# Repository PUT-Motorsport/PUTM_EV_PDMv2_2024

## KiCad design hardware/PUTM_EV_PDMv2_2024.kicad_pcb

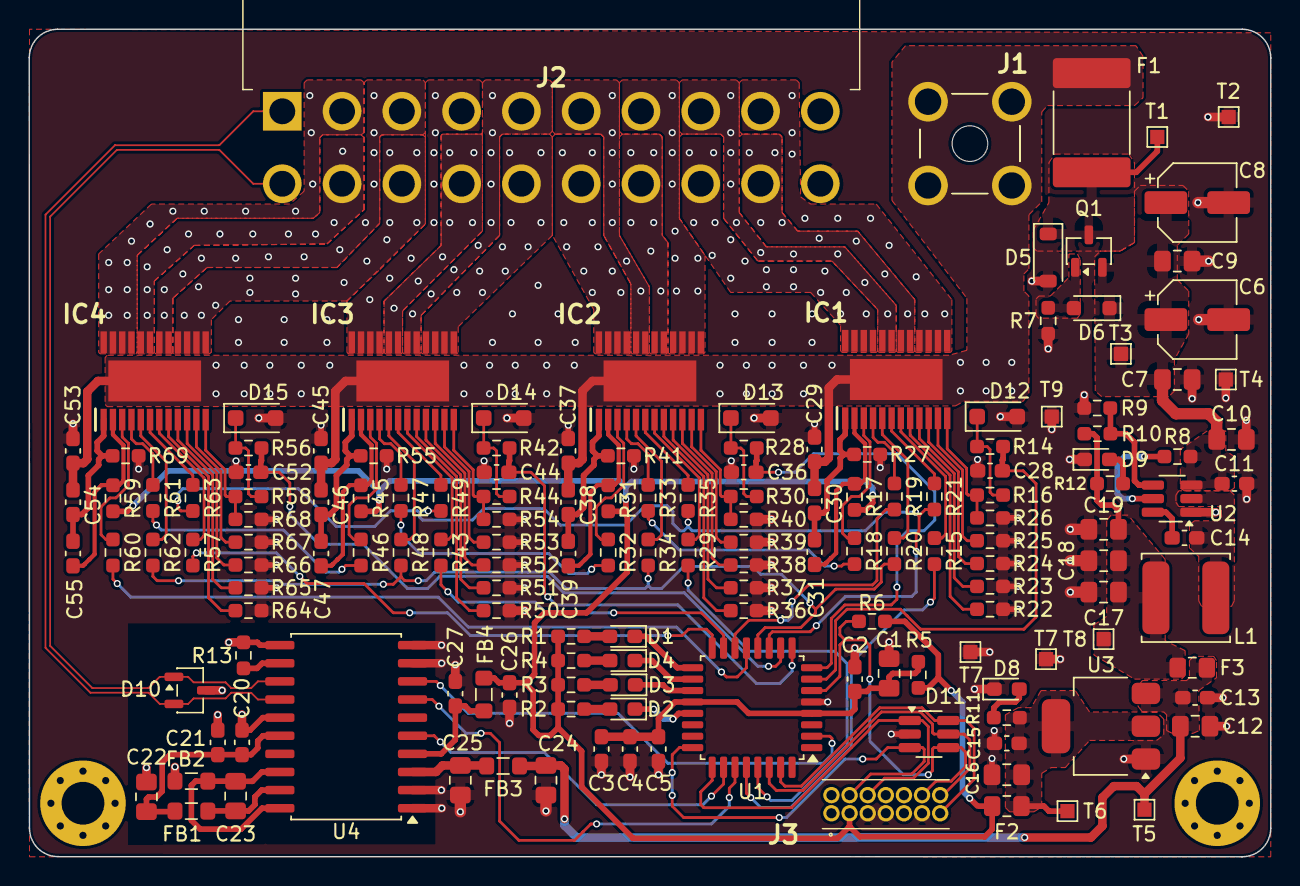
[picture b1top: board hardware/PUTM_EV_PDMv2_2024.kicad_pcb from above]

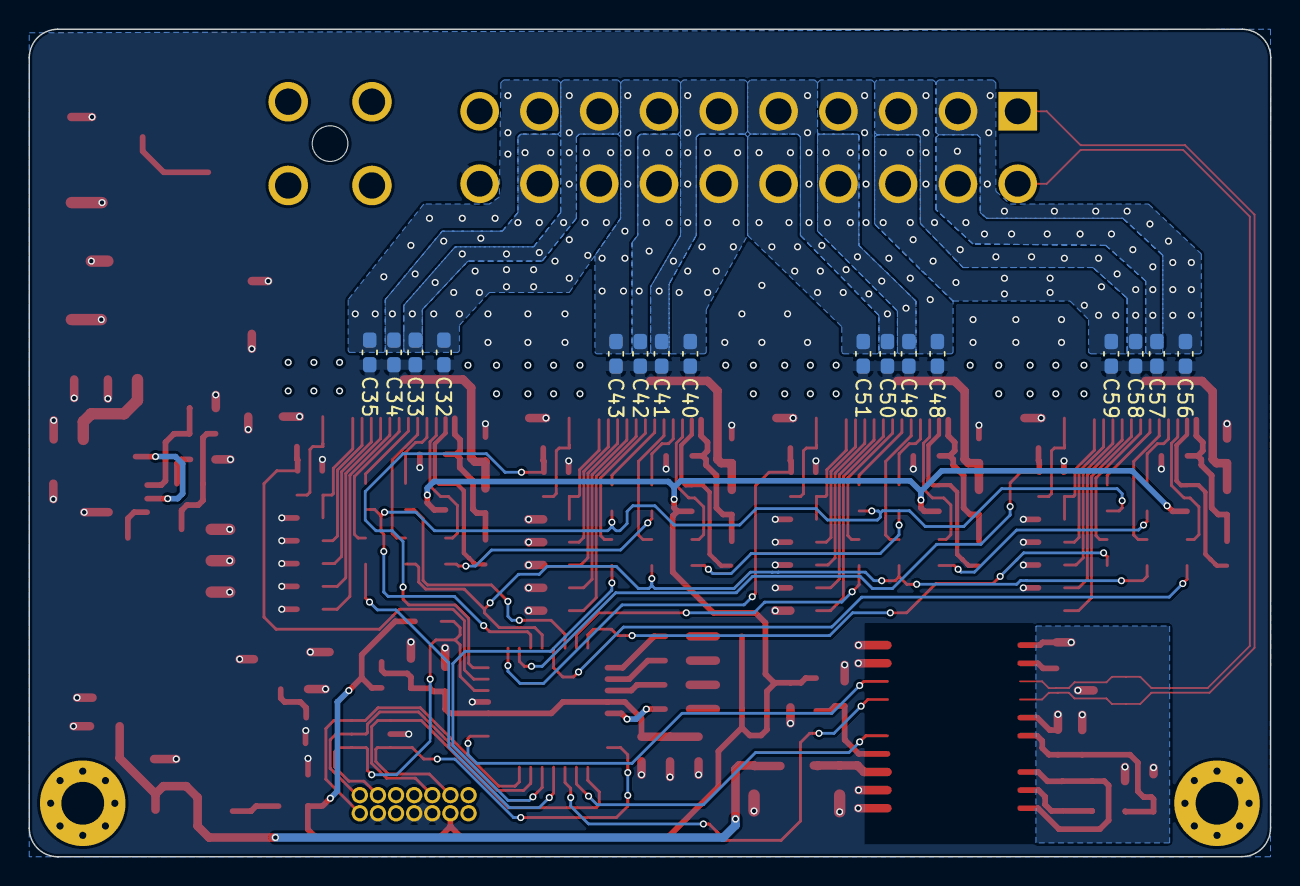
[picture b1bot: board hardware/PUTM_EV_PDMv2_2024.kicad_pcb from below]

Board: 4 copper layers, 87.0 x 58.0 mm, 172 parts (16 on the bottom side), 124 nets.

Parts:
C1, C7, C9, C12: 10u; C_0805_2012Metric_Pad1.18x1.45mm_HandSolder
C2, C3: 4u7; C_0603_1608Metric_Pad1.08x0.95mm_HandSolder
C4, C5, C11, C13, C14, C15, C20, C26, C29, C37, C45, C53: 100n; C_0603_1608Metric_Pad1.08x0.95mm_HandSolder
C6, C8: 22u; CP_Elec_5x5.8
C10, C16, C17, C18, C19: 22u; C_0805_2012Metric_Pad1.18x1.45mm_HandSolder
C21, C27, C32, C33, C34, C35, C40, C41, C42, C43, C48, C49, C50, C51, C56, C57, C58, C59: 10n; C_0603_1608Metric_Pad1.08x0.95mm_HandSolder
C22, C23, C24, C25: 47u; C_0805_2012Metric_Pad1.18x1.45mm_HandSolder
C28, C36, C44, C52: 220p; C_0603_1608Metric_Pad1.08x0.95mm_HandSolder
C30, C38, C46, C54: 22n; C_0603_1608Metric_Pad1.08x0.95mm_HandSolder
C31, C39, C47, C55: 470n; C_0603_1608Metric_Pad1.08x0.95mm_HandSolder
D1, D2, D3, D4: LED_Debug; LED_0603_1608Metric_Pad1.05x0.95mm_HandSolder
D5: 30V/200W; D_SOD-123
D6: 9V1/200mW; D_SOD-323_HandSoldering
D8: LED_+3V3; LED_0603_1608Metric_Pad1.05x0.95mm_HandSolder
D9: LED_+5V; LED_0603_1608Metric_Pad1.05x0.95mm_HandSolder
D10: PESD5V0L2BT,215; SOT-23-3
D11: SP0505BAHTG; SOT-23-6_Handsoldering
D12, D13, D14, D15: 40V/3A; D_SOD-123F
F1: 33V/1A5; Fuse_2920_7451Metric_Pad2.10x5.45mm_HandSolder
F2, F3: 6V/1A; Fuse_0805_2012Metric_Pad1.15x1.40mm_HandSolder
FB1, FB2, FB3, FB4: 2K@100MHz; L_0805_2012Metric_Pad1.05x1.20mm_HandSolder
IC1, IC2, IC3, IC4: BTS722204ESAXUMA1; SOP65P600X115-25N
J1: 74650073R
J2: IPBS-110-01-XX-D-GP; IPBT110H1TDRAGP
J3: FTSH-107-01-L-D-K; FTSH-107-XX-YYY-D-K
L1: 68u/1A4; L_TDK_VLS6045EX_VLS6045AF
Q1: 30V/5A; SOT-23-3
R1, R2, R3, R4: 150R; R_0603_1608Metric_Pad0.98x0.95mm_HandSolder
R5: 0; R_0603_1608Metric_Pad0.98x0.95mm_HandSolder
R6, R7, R10, R13: 100k; R_0603_1608Metric_Pad0.98x0.95mm_HandSolder
R8: 510k; R_0603_1608Metric_Pad0.98x0.95mm_HandSolder
R9: 13k3; R_0603_1608Metric_Pad0.98x0.95mm_HandSolder
R11, R12: 1k; R_0603_1608Metric_Pad0.98x0.95mm_HandSolder
R14, R15, R16, R28, R29, R30, R42, R43, R44, R56, R57, R58: 4k7; R_0603_1608Metric_Pad0.98x0.95mm_HandSolder
R17, R31, R45, R59: 470R; R_0603_1608Metric_Pad0.98x0.95mm_HandSolder
R18, R19, R20, R21, R32, R33, R34, R35, R46, R47, R48, R49, R60, R61, R62, R63: 330R; R_0603_1608Metric_Pad0.98x0.95mm_HandSolder
R22, R23, R24, R25, R36, R37, R38, R39, R50, R51, R52, R53, R64, R65, R66, R67: 10k; R_0603_1608Metric_Pad0.98x0.95mm_HandSolder
R26, R40, R54, R68: 1k2; R_0603_1608Metric_Pad0.98x0.95mm_HandSolder
R27, R41, R55, R69: 47R; R_0603_1608Metric_Pad0.98x0.95mm_HandSolder
T1, T3: TP_VCC; TestPoint_Pad_1.0x1.0mm
T2, T4, T7, T7#2, T9: TP_GND; TestPoint_Pad_1.0x1.0mm
T5, T8: TP_+5V; TestPoint_Pad_1.0x1.0mm
T6: TP_+3V3; TestPoint_Pad_1.0x1.0mm
U1: STM32G0C1KCTxN; LQFP-32_7x7mm_P0.8mm
U2: TPS54202HDDCR; SOT-23-6_Handsoldering
U3: LM1117-3.3; SOT-223-3_TabPin2
U4: ADM3057ExRW; SOIC-20W_7.5x12.8mm_P1.27mm

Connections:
+3V3: C26.1, F2.2, FB4.2, J3.3, R1.2, R2.2, R3.2, R4.2, R5.1, R6.1, R17.1, R31.1, R45.1, R59.1
+5V: C12.1, C13.1, C24.2, F3.1, FB3.2, T5.1, U3.3 (VI)
+24V: C6.1, C7.1, C8.1, C9.1, C10.1, C11.2, D6.1 (K), Q1.2 (S), R8.2, T3.1, U2.3 (VIN)
+BATT: C29.1, C30.1, C37.1, C38.1, C45.1, C46.1, C53.1, C54.1, F1.2, IC1.25 (VS), IC2.25 (VS), IC3.25 (VS), IC4.25 (VS), J1.1, J1.2, J1.3, J1.4
/CAN/CAN.N: D10.1 (A1), J2.11, U4.13 (CANL)
/CAN/CAN.P: D10.2 (A2), J2.1, U4.14 (CANH)
/CAN/CAN.RX: U1.26 (FDCAN1_RX), U4.5 (RXD)
/CAN/CAN.TX: U1.27 (FDCAN1_TX), U4.7 (TXD)
/CAN/CAN_GND_ISO: C20.1, C21.2, C22.1, D10.3 (common), FB2.2, R13.1, U4.11 (GND2), U4.15 (GND2)
/CAN/GNDISO: C23.1, FB2.1, U4.18 (GNDISO), U4.20 (GNDISO)
/CAN/RS: R13.2, U4.12 (RS)
/CAN/STBY_CAN: U1.2 (PC14), U4.8 (STBY)
/CAN/VCC: C25.1, FB3.1, U4.3 (VCC)
/CAN/VIO: C27.1, FB4.1, U4.4 (VIO)
/CAN/VISOIN: C20.2, C21.1, C22.2, FB1.1, U4.16 (VISOIN)
/CAN/VISOOUT: C23.2, FB1.2, U4.19 (VISOOUT)
/Connectors/RST: D11.4 (K), J3.12, R6.2, U1.6 (PF2)
/Connectors/SW.CLK: D11.1 (K), J3.6, U1.25 (SYS_SWCLK)
/Connectors/SW.DIO: D11.3 (K), J3.4, U1.24 (SYS_SWDIO)
/Connectors/USART.RX: D11.6 (K), J3.13, U1.31 (USART1_RX)
/Connectors/USART.TX: D11.5 (K), J3.14, U1.30 (USART1_TX)
/MCU/FUSE_IS0: C28.1, R14.1, U1.7 (PA0)
/MCU/FUSE_IS1: C36.1, R28.1, U1.8 (PA1)
/MCU/FUSE_IS2: C44.1, R42.1, U1.9 (PA2)
/MCU/FUSE_IS3: C52.1, R56.1, U1.10 (PA3)
/MCU/LD_0_R: D4.2 (A), R4.1
/MCU/LD_1_R: D3.2 (A), R3.1
/MCU/LD_2_R: D2.2 (A), R2.1
/MCU/LD_3_R: D1.2 (A), R1.1
/MCU/LED0: D4.1 (K), U1.18 (PA8)
/MCU/LED1: D3.1 (K), U1.19 (PA9/UCPD1_DBCC1)
/MCU/LED2: D2.1 (K), U1.21 (PA10/UCPD1_DBCC2)
/MCU/LED3: D1.1 (K), U1.17 (PB15)
/MCU/LHI0: R15.1, U1.28 (PD2)
/MCU/LHI1: R29.1, U1.29 (PD3)
/MCU/LHI2: R43.1, U1.15 (PB0)
/MCU/LHI3: R57.1, U1.16 (PB1)
/MCU/SPI.MISO: R60.1, U1.13 (SPI1_MISO)
/MCU/SPI.MOSI: R19.1, U1.14 (SPI1_MOSI)
/MCU/SPI.NSS: R21.1, R35.1, R49.1, R63.1, U1.11 (SPI1_NSS)
/MCU/SPI.SCK: R20.1, R34.1, R48.1, R62.1, U1.12 (SPI1_SCK)
/MCU/STM_VCC: C1.1, C2.1, C3.1, C4.1, C5.1, R5.2, U1.4 (VDD), U1.20 (VDDIO2)
/Power controllers/IC_0/CSN: IC1.6 (CSN), R21.2
/Power controllers/IC_0/IN0: IC1.8 (IN0), R22.2
/Power controllers/IC_0/IN1: IC1.9 (IN1), R23.2
/Power controllers/IC_0/IN2: IC1.10 (IN2), R24.2
/Power controllers/IC_0/IN3: IC1.11 (IN3), R25.2
/Power controllers/IC_0/IS: IC1.12 (IS), R16.2, R26.1
/Power controllers/IC_0/LHI: IC1.7 (LHI), R15.2
/Power controllers/IC_0/MISO: R18.1, R33.1
/Power controllers/IC_0/PC0_GND: C30.2, C31.1, IC1.1 (GND), R27.2
/Power controllers/IC_0/R_IS_PROT: D12.1 (K), R14.2, R16.1
/Power controllers/IC_0/SCLK: IC1.5 (SCLK), R20.2
/Power controllers/IC_0/SI: IC1.4 (SI), R19.2
/Power controllers/IC_0/SO: IC1.3 (SO), R18.2
/Power controllers/IC_0/VDD: C31.2, IC1.2 (VDD), R17.2
/Power controllers/IC_1/CSN: IC2.6 (CSN), R35.2
/Power controllers/IC_1/IN0: IC2.8 (IN0), R36.2
/Power controllers/IC_1/IN1: IC2.9 (IN1), R37.2
/Power controllers/IC_1/IN2: IC2.10 (IN2), R38.2
/Power controllers/IC_1/IN3: IC2.11 (IN3), R39.2
/Power controllers/IC_1/IS: IC2.12 (IS), R30.2, R40.1
/Power controllers/IC_1/LHI: IC2.7 (LHI), R29.2
/Power controllers/IC_1/MISO: R32.1, R47.1
/Power controllers/IC_1/PC1_GND: C38.2, C39.1, IC2.1 (GND), R41.2
/Power controllers/IC_1/R_IS_PROT: D13.1 (K), R28.2, R30.1
/Power controllers/IC_1/SCLK: IC2.5 (SCLK), R34.2
/Power controllers/IC_1/SI: IC2.4 (SI), R33.2
/Power controllers/IC_1/SO: IC2.3 (SO), R32.2
/Power controllers/IC_1/VDD: C39.2, IC2.2 (VDD), R31.2
/Power controllers/IC_2/CSN: IC3.6 (CSN), R49.2
/Power controllers/IC_2/IN0: IC3.8 (IN0), R50.2
/Power controllers/IC_2/IN1: IC3.9 (IN1), R51.2
/Power controllers/IC_2/IN2: IC3.10 (IN2), R52.2
/Power controllers/IC_2/IN3: IC3.11 (IN3), R53.2
/Power controllers/IC_2/IS: IC3.12 (IS), R44.2, R54.1
/Power controllers/IC_2/LHI: IC3.7 (LHI), R43.2
/Power controllers/IC_2/MISO: R46.1, R61.1
/Power controllers/IC_2/PC2_GND: C46.2, C47.1, IC3.1 (GND), R55.2
/Power controllers/IC_2/R_IS_PROT: D14.1 (K), R42.2, R44.1
/Power controllers/IC_2/SCLK: IC3.5 (SCLK), R48.2
/Power controllers/IC_2/SI: IC3.4 (SI), R47.2
/Power controllers/IC_2/SO: IC3.3 (SO), R46.2
/Power controllers/IC_2/VDD: C47.2, IC3.2 (VDD), R45.2
/Power controllers/IC_3/CSN: IC4.6 (CSN), R63.2
/Power controllers/IC_3/IN0: IC4.8 (IN0), R64.2
/Power controllers/IC_3/IN1: IC4.9 (IN1), R65.2
/Power controllers/IC_3/IN2: IC4.10 (IN2), R66.2
/Power controllers/IC_3/IN3: IC4.11 (IN3), R67.2
/Power controllers/IC_3/IS: IC4.12 (IS), R58.2, R68.1
/Power controllers/IC_3/LHI: IC4.7 (LHI), R57.2
/Power controllers/IC_3/PC3_GND: C54.2, C55.1, IC4.1 (GND), R69.2
/Power controllers/IC_3/R_IS_PROT: D15.1 (K), R56.2, R58.1
/Power controllers/IC_3/SCLK: IC4.5 (SCLK), R62.2
/Power controllers/IC_3/SI: IC4.4 (SI), R61.2
/Power controllers/IC_3/SO: IC4.3 (SO), R60.2
/Power controllers/IC_3/VDD: C55.2, IC4.2 (VDD), R59.2
/Power/+5V_OUT: C17.1, C18.1, C19.1, F3.2, L1.2, R10.2, R12.1, T8.1
/Power/BOOT_+5V: C14.1, U2.6 (BOOT)
/Power/D3V3_R1k: D8.2 (A), R11.2
/Power/D5V_R1k: D9.2 (A), R12.2
/Power/EN: R8.1, U2.5 (EN)
/Power/FB_+5V: R9.2, R10.1, U2.4 (FB)
/Power/RPP_D: D5.1 (K), F1.1, Q1.3 (D), T1.1
/Power/RPP_G: D6.2 (A), Q1.1 (G), R7.2
/Power/SW_+5V: C14.2, L1.1, U2.2 (SW)
/Power/VO_+3.3V: C15.1, C16.1, F2.1, R11.1, T6.1, U3.2 (VO)
GND: C1.2, C2.2, C3.2, C4.2, C5.2, C6.2, C7.2, C8.2, C9.2, C10.2, C11.1, C12.2, C13.2, C15.2, C16.2, C17.2, C18.2, C19.2, C24.1, C25.2, C26.2, C27.2, C28.2, C29.2, C32.2, C33.2, C34.2, C35.2, C36.2, C37.2, C40.2, C41.2, C42.2, C43.2, C44.2, C45.2, C48.2, C49.2, C50.2, C51.2, C52.2, C53.2, C56.2, C57.2, C58.2, C59.2, D5.2 (A), D8.1 (K), D9.1 (K), D11.2 (A), D12.2 (A), D13.2 (A), D14.2 (A), D15.2 (A), J2.20, J3.5, J3.7, J3.11, R7.1, R9.1, R22.1, R23.1, R24.1, R25.1, R26.2, R27.1, R36.1, R37.1, R38.1, R39.1, R40.2, R41.1, R50.1, R51.1, R52.1, R53.1, R54.2, R55.1, R64.1, R65.1, R66.1, R67.1, R68.2, R69.1, T2.1, T4.1, T7.1, T7#2.1, T9.1, U1.5 (VSS), U2.1 (GND), U3.1 (GND), U4.1 (GND1), U4.2 (GND1), U4.9 (AUXIN), U4.10 (GND1)
OUT0_0: C32.1, IC1.21 (OUT0_1), IC1.22 (OUT0_2), IC1.23 (OUT0_3), IC1.24 (OUT0_4), J2.18
OUT0_1: C33.1, IC1.19 (OUT1_1), IC1.20 (OUT1_2), J2.8
OUT0_2: C34.1, IC1.17 (OUT2_1), IC1.18 (OUT2_2), J2.19
OUT0_3: C35.1, IC1.13 (OUT3_1), IC1.14 (OUT3_2), IC1.15 (OUT3_3), IC1.16 (OUT3_4), J2.9
OUT1_0: C40.1, IC2.21 (OUT0_1), IC2.22 (OUT0_2), IC2.23 (OUT0_3), IC2.24 (OUT0_4), J2.16
OUT1_1: C41.1, IC2.19 (OUT1_1), IC2.20 (OUT1_2), J2.6
OUT1_2: C42.1, IC2.17 (OUT2_1), IC2.18 (OUT2_2), J2.17
OUT1_3: C43.1, IC2.13 (OUT3_1), IC2.14 (OUT3_2), IC2.15 (OUT3_3), IC2.16 (OUT3_4), J2.7
OUT2_0: C48.1, IC3.21 (OUT0_1), IC3.22 (OUT0_2), IC3.23 (OUT0_3), IC3.24 (OUT0_4), J2.4
OUT2_1: C49.1, IC3.19 (OUT1_1), IC3.20 (OUT1_2), J2.14
OUT2_2: C50.1, IC3.17 (OUT2_1), IC3.18 (OUT2_2), J2.5
OUT2_3: C51.1, IC3.13 (OUT3_1), IC3.14 (OUT3_2), IC3.15 (OUT3_3), IC3.16 (OUT3_4), J2.15
OUT3_0: C56.1, IC4.21 (OUT0_1), IC4.22 (OUT0_2), IC4.23 (OUT0_3), IC4.24 (OUT0_4), J2.2
OUT3_1: C57.1, IC4.19 (OUT1_1), IC4.20 (OUT1_2), J2.12
OUT3_2: C58.1, IC4.17 (OUT2_1), IC4.18 (OUT2_2), J2.3
OUT3_3: C59.1, IC4.13 (OUT3_1), IC4.14 (OUT3_2), IC4.15 (OUT3_3), IC4.16 (OUT3_4), J2.13

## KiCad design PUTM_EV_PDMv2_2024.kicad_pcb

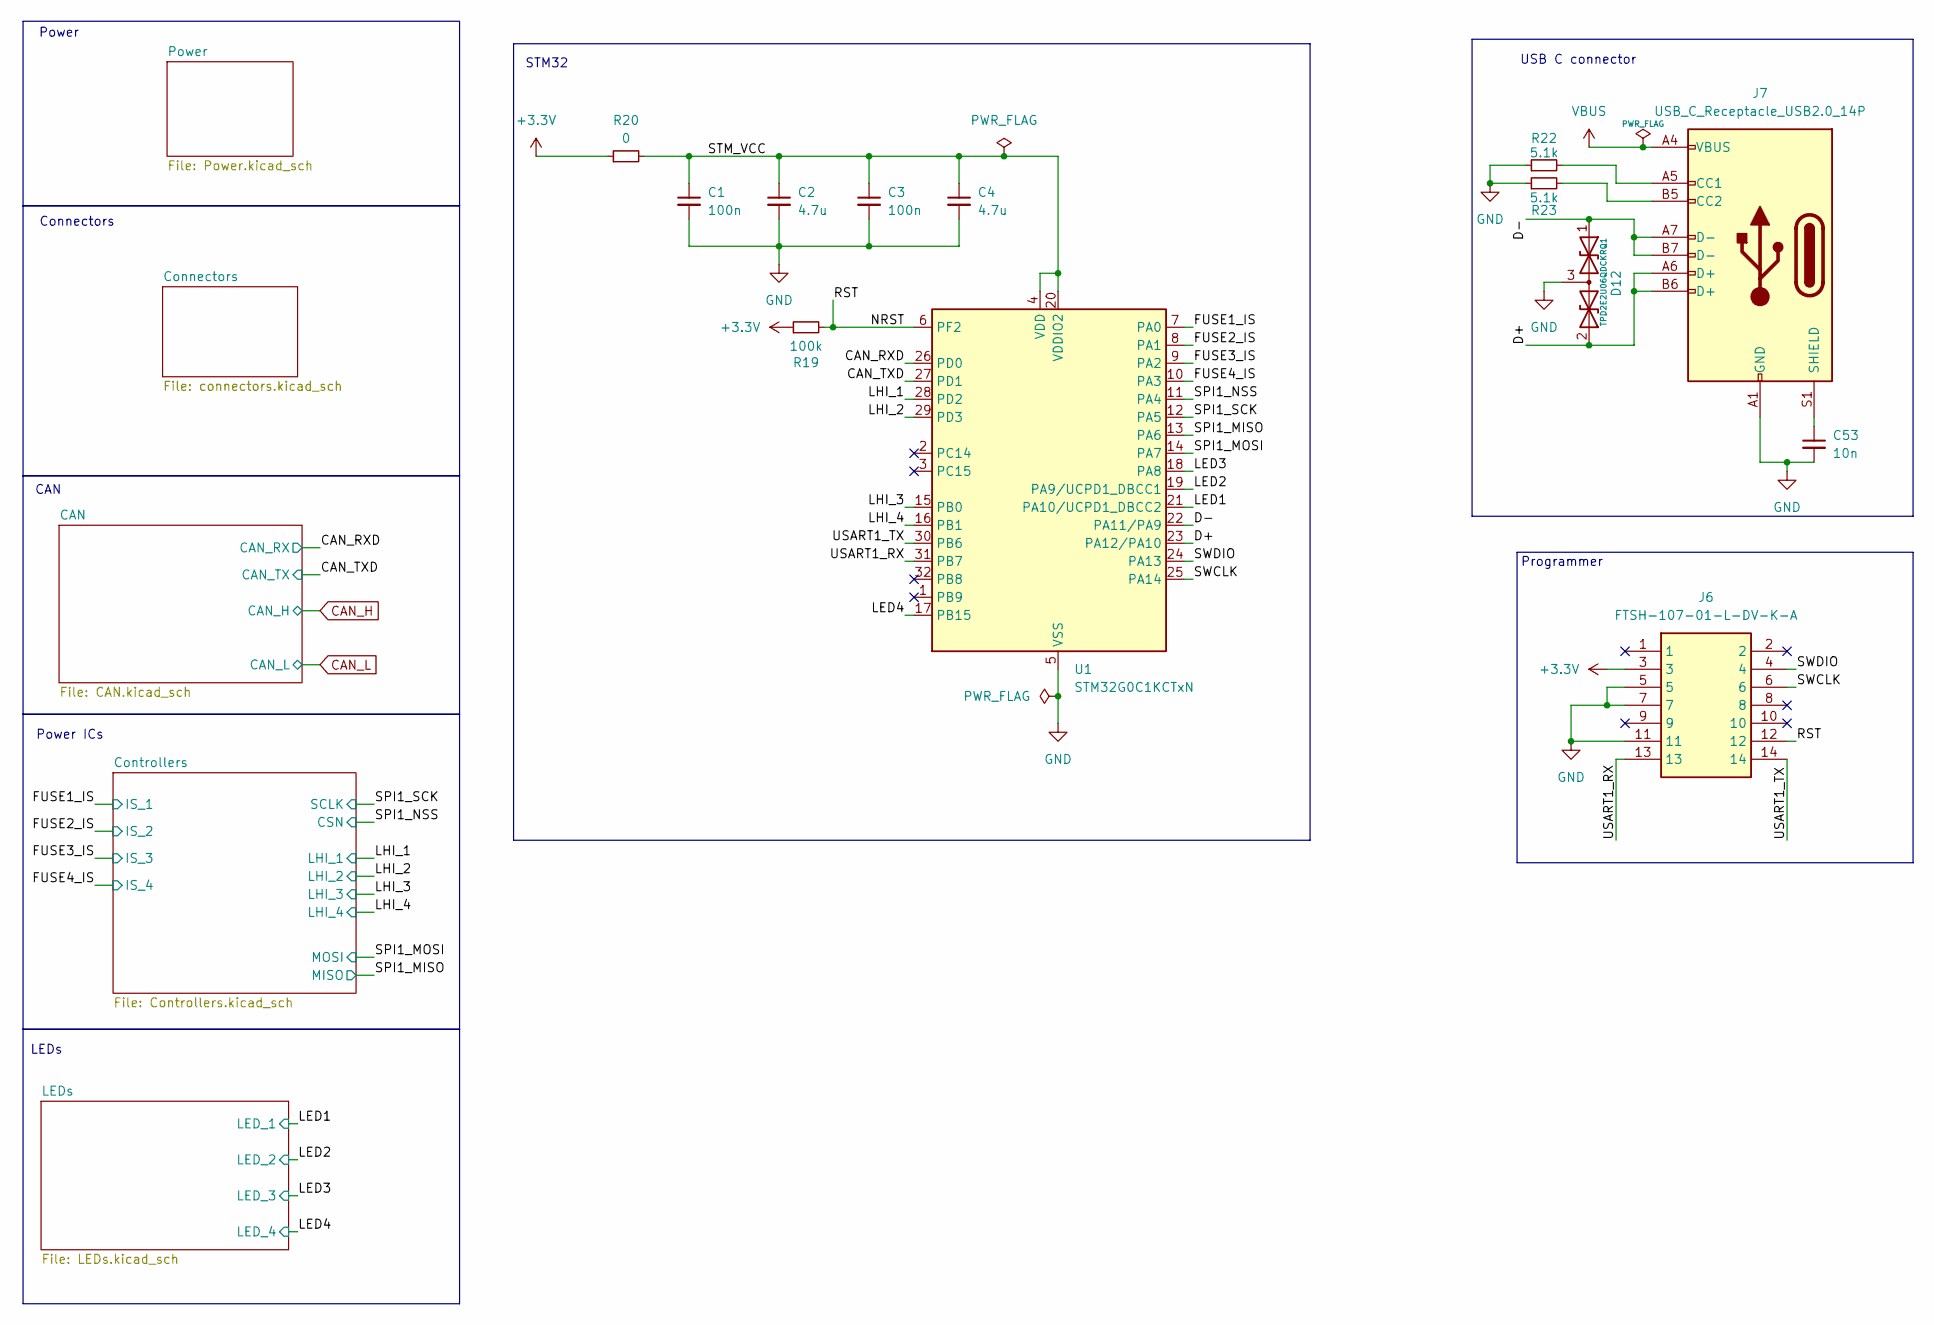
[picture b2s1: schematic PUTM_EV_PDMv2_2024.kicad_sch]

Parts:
C1, C3: 100n; C_0603_1608Metric
C2, C4: 4.7u; C_0603_1608Metric
C53: 10n; C_0603_1608Metric_Pad1.08x0.95mm_HandSolder
D12: TPD2E2U06QDCKRQ1; SOT-323_SC-70_Handsoldering
J6: FTSH-107-01-L-DV-K-A; FTSH-107-XX-YYY-DV-K-A; Mouser Part Number 200-FTSH10701LDVKA
J7: USB_C_Receptacle_USB2.0_14P; USB_C_Receptacle_JAE_DX07S024WJ3R400
R19: 100k; R_0603_1608Metric
R20: 0; R_0603_1608Metric_Pad0.98x0.95mm_HandSolder
R22, R23: 5.1k; R_0603_1608Metric_Pad0.98x0.95mm_HandSolder
U1: STM32G0C1KCTxN; LQFP-32_7x7mm_P0.8mm

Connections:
+3.3V: J6.3, R19.1, R20.1; also elsewhere on the board
/CAN_RXD: U1.26 (PD0); also elsewhere on the board
/CAN_TXD: U1.27 (PD1); also elsewhere on the board
/D+: D12.2 (A2), J7.A6 (D+), J7.B6 (D+), U1.23 (PA12/PA10)
/D-: D12.1 (A1), J7.A7 (D-), J7.B7 (D-), U1.22 (PA11/PA9)
/FUSE1_IS: U1.7 (PA0); also elsewhere on the board
/FUSE2_IS: U1.8 (PA1); also elsewhere on the board
/FUSE3_IS: U1.9 (PA2); also elsewhere on the board
/FUSE4_IS: U1.10 (PA3); also elsewhere on the board
/LED1: U1.21 (PA10/UCPD1_DBCC2); also elsewhere on the board
/LED2: U1.19 (PA9/UCPD1_DBCC1); also elsewhere on the board
/LED3: U1.18 (PA8); also elsewhere on the board
/LED4: U1.17 (PB15); also elsewhere on the board
/LHI_1: U1.28 (PD2); also elsewhere on the board
/LHI_2: U1.29 (PD3); also elsewhere on the board
/LHI_3: U1.15 (PB0); also elsewhere on the board
/LHI_4: U1.16 (PB1); also elsewhere on the board
/NRST: J6.12, R19.2, U1.6 (PF2)
/SPI1_MISO: U1.13 (PA6); also elsewhere on the board
/SPI1_MOSI: U1.14 (PA7); also elsewhere on the board
/SPI1_NSS: U1.11 (PA4); also elsewhere on the board
/SPI1_SCK: U1.12 (PA5); also elsewhere on the board
/STM_VCC: C1.1, C2.1, C3.1, C4.1, R20.2, U1.4 (VDD), U1.20 (VDDIO2)
/SWCLK: J6.6, U1.25 (PA14)
/SWDIO: J6.4, U1.24 (PA13)
/USART1_RX: J6.13, U1.31 (PB7)
/USART1_TX: J6.14, U1.30 (PB6)
GND: C1.2, C2.2, C3.2, C4.2, C53.2, D12.3 (common), J6.5, J6.7, J6.11, J7.A1 (GND), J7.A12 (GND), J7.B1 (GND), J7.B12 (GND), R22.1, R23.1, U1.5 (VSS); also elsewhere on the board
unnamed: J7.A5 (CC1), R22.2
unnamed: J7.B5 (CC2), R23.2
unnamed: C53.1, J7.S1 (SHIELD)
VBUS: J7.A4 (VBUS), J7.A9 (VBUS), J7.B4 (VBUS), J7.B9 (VBUS); also elsewhere on the board

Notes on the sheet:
Connectors
CAN
Programmer
LEDs
STM32
USB C connector
Power
Power ICs

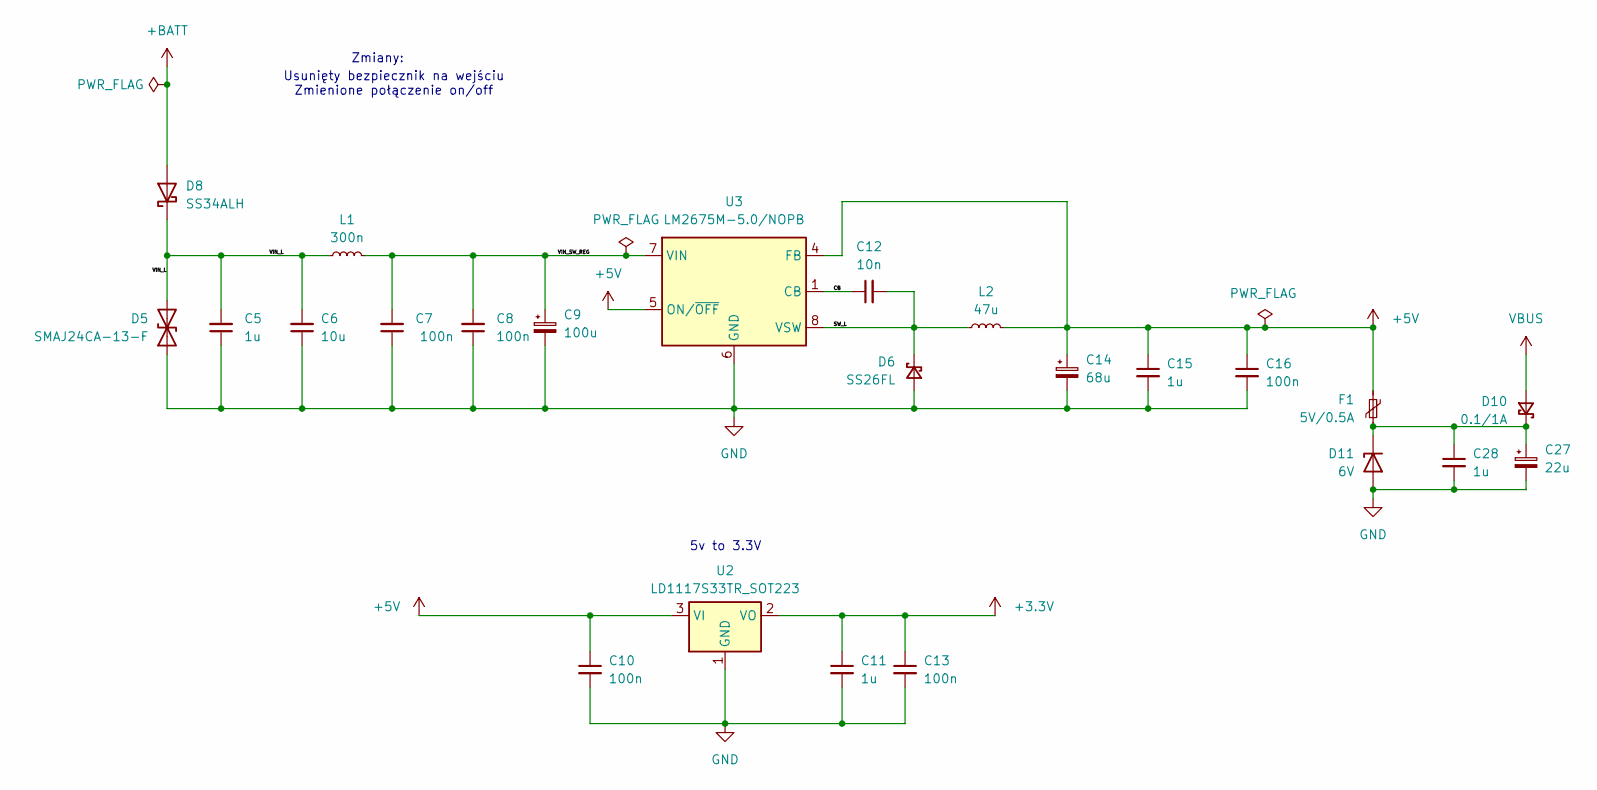
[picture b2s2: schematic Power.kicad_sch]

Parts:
C5, C11, C15: 1u; C_0603_1608Metric
C6: 10u; C_0603_1608Metric
C7, C8, C10, C13, C16: 100n; C_0603_1608Metric
C9: 100u; CP_Elec_6.3x7.7
C12: 10n; C_0603_1608Metric
C14: 68u; CP_Elec_6.3x5.4
C27: 22u; CP_Elec_4x4.5
C28: 1u; C_0603_1608Metric_Pad1.08x0.95mm_HandSolder
D5: SMAJ24CA-13-F; D_SMA; Mouser Part Number 621-SMAJ24CA-13-F
D6: SS26FL; D_SOD-123
D8: SS34ALH; D_SMA
D10: 0.1/1A; D_SMA
D11: 6V; D_SOD-123
F1: 5V/0.5A; Fuse_1206_3216Metric_Pad1.42x1.75mm_HandSolder
L1: 300n; L_0603_1608Metric
L2: 47u; L_6.3x6.3_H3
U2: LD1117S33TR_SOT223; SOT-223-3_TabPin2
U3: LM2675M-5.0/NOPB; SOIC-8_3.9x4.9mm_P1.27mm

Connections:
+3.3V: C11.1, C13.1, U2.2 (VO); also elsewhere on the board
+5V: C10.1, C14.1, C15.1, C16.1, F1.1, L2.2, U2.3 (VI), U3.4 (FB), U3.5 (ON/~OFF); also elsewhere on the board
+BATT: D8.2 (A); also elsewhere on the board
/Power/CB: C12.1, U3.1 (CB)
/Power/SW_L: C12.2, D6.1 (K), L2.1, U3.8 (VSW)
/Power/VIN_L: C5.2, C6.2, D5.2 (A2), D8.1 (K), L1.1
/Power/VIN_SW_REG: C7.2, C8.2, C9.1, L1.2, U3.7 (VIN)
GND: C5.1, C6.1, C7.1, C8.1, C9.2, C10.2, C11.2, C13.2, C14.2, C15.2, C16.2, C27.2, C28.2, D5.1 (A1), D6.2 (A), D11.2 (A), U2.1 (GND), U3.6 (GND); also elsewhere on the board
unnamed: C27.1, C28.1, D10.1 (K), D11.1 (K), F1.2
VBUS: D10.2 (A); also elsewhere on the board

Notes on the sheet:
Zmiany:
Usunięty bezpiecznik na wejściu Zmienione połączenie on/off
5v to 3.3V

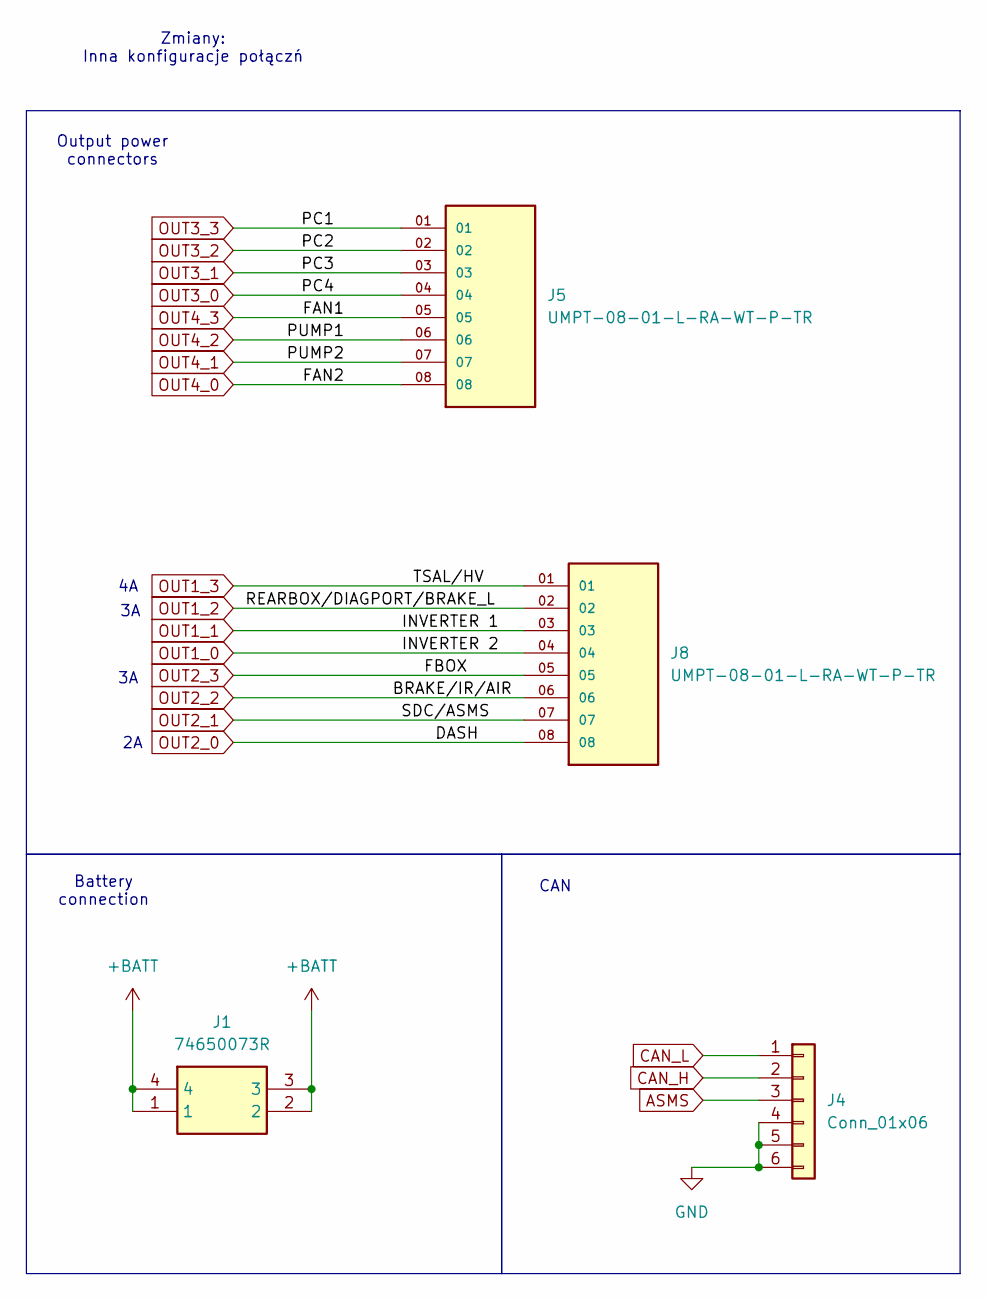
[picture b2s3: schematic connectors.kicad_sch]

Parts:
J1: 74650073R; Mouser Part Number 710-74650073R
J4: Conn_01x06; IDC-Header_2x03_P2.54mm_Vertical
J5, J8: UMPT-08-01-L-RA-WT-P-TR; SAMTEC_UMPT-08-01-L-RA-WT-P-TR

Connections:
+BATT: J1.1, J1.2, J1.3, J1.4; also elsewhere on the board
ASMS: J4.3
CAN_H: J4.2; also elsewhere on the board
CAN_L: J4.1; also elsewhere on the board
GND: J4.4, J4.5, J4.6; also elsewhere on the board
OUT1_0: J8.04; also elsewhere on the board
OUT1_1: J8.03; also elsewhere on the board
OUT1_2: J8.02; also elsewhere on the board
OUT1_3: J8.01; also elsewhere on the board
OUT2_0: J8.08; also elsewhere on the board
OUT2_1: J8.07; also elsewhere on the board
OUT2_2: J8.06; also elsewhere on the board
OUT2_3: J8.05; also elsewhere on the board
OUT3_0: J5.04; also elsewhere on the board
OUT3_1: J5.03; also elsewhere on the board
OUT3_2: J5.02; also elsewhere on the board
OUT3_3: J5.01; also elsewhere on the board
OUT4_0: J5.08; also elsewhere on the board
OUT4_1: J5.07; also elsewhere on the board
OUT4_2: J5.06; also elsewhere on the board
OUT4_3: J5.05; also elsewhere on the board

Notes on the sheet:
CAN
Battery connection
Output power connectors
Zmiany: Inna konfiguracje połączń

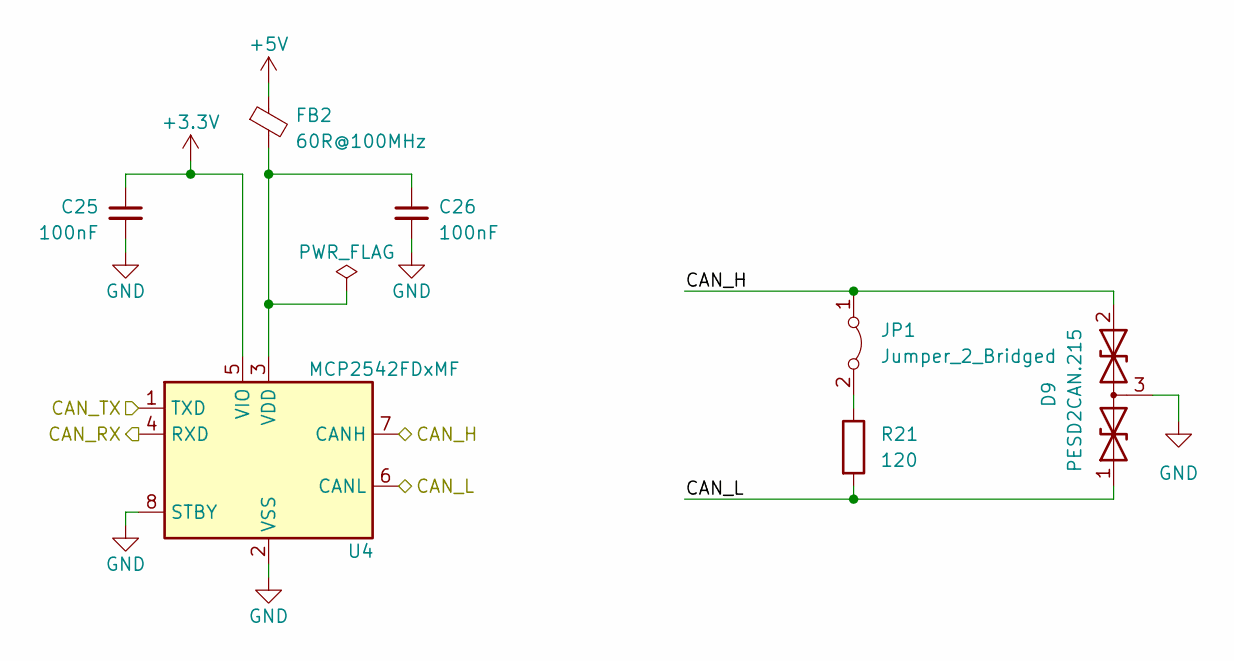
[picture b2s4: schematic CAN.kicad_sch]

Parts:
C25, C26: 100nF; C_0603_1608Metric_Pad1.08x0.95mm_HandSolder
D9: PESD2CAN.215; SOT-23
FB2: 60R@100MHz; L_0603_1608Metric
JP1: Jumper_2_Bridged; PinHeader_1x02_P2.54mm_Vertical
R21: 120; R_0603_1608Metric_Pad0.98x0.95mm_HandSolder
U4: MCP2542FDxMF; DFN-8-1EP_3x3mm_P0.65mm_EP1.55x2.4mm

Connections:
+3.3V: C25.1, U4.5 (VIO); also elsewhere on the board
+5V: FB2.1; also elsewhere on the board
/CAN_RXD: U4.4 (RXD); also elsewhere on the board
/CAN_TXD: U4.1 (TXD); also elsewhere on the board
CAN_H: D9.2 (A2), JP1.1 (A), U4.7 (CANH); also elsewhere on the board
CAN_L: D9.1 (A1), R21.2, U4.6 (CANL); also elsewhere on the board
GND: C25.2, C26.2, D9.3 (common), U4.2 (VSS), U4.8 (STBY), U4.9 (VSS); also elsewhere on the board
unnamed: JP1.2 (B), R21.1
unnamed: C26.1, FB2.2, U4.3 (VDD)

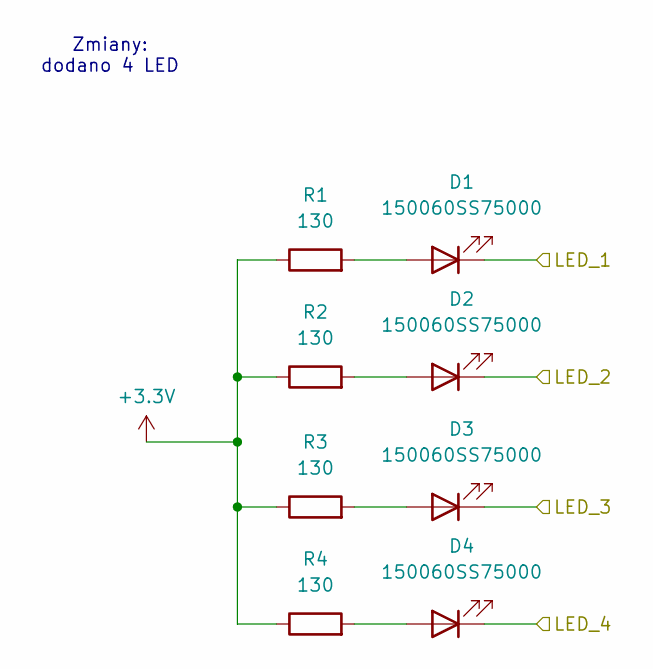
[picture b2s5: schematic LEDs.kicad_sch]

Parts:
D1, D2, D3, D4: 150060SS75000; LED_0603_1608Metric
R1, R2, R3, R4: 130; R_0603_1608Metric

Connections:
+3.3V: R1.1, R2.1, R3.1, R4.1; also elsewhere on the board
/LED1: D1.1 (K); also elsewhere on the board
/LED2: D2.1 (K); also elsewhere on the board
/LED3: D3.1 (K); also elsewhere on the board
/LED4: D4.1 (K); also elsewhere on the board
unnamed: D2.2 (A), R2.2
unnamed: D4.2 (A), R4.2

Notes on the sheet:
Zmiany: dodano 4 LED

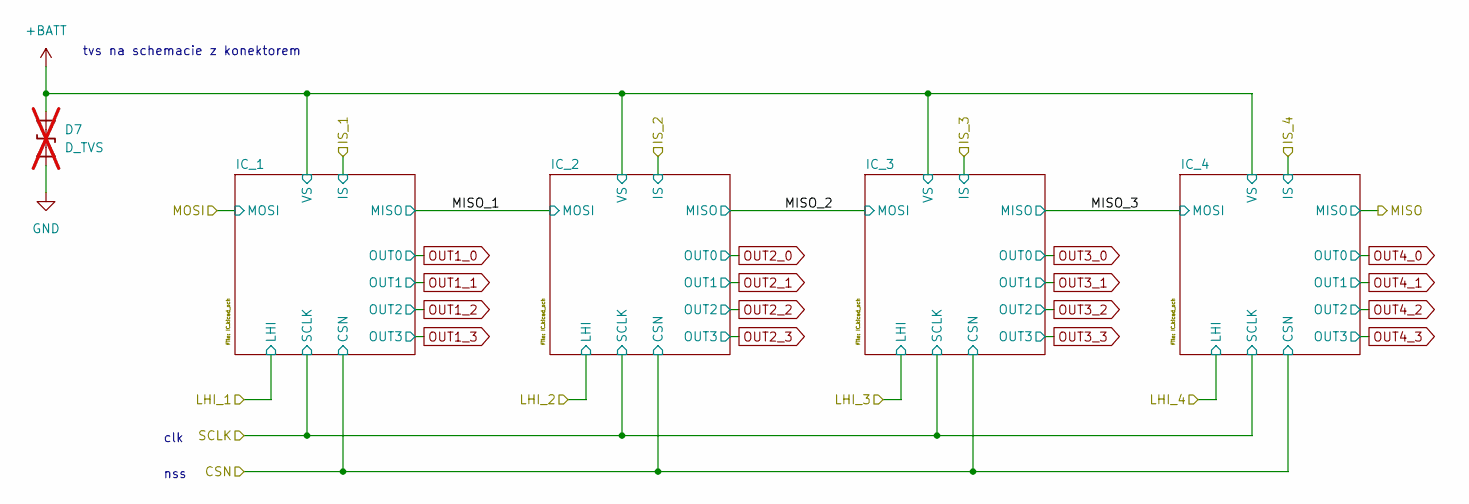
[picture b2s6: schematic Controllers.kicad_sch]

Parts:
D7: D_TVS; not fitted

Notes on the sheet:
nss
clk
tvs na schemacie z konektorem
